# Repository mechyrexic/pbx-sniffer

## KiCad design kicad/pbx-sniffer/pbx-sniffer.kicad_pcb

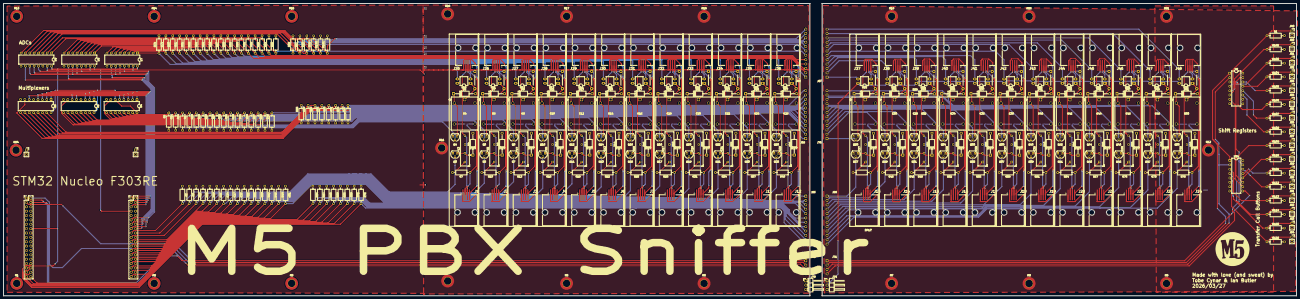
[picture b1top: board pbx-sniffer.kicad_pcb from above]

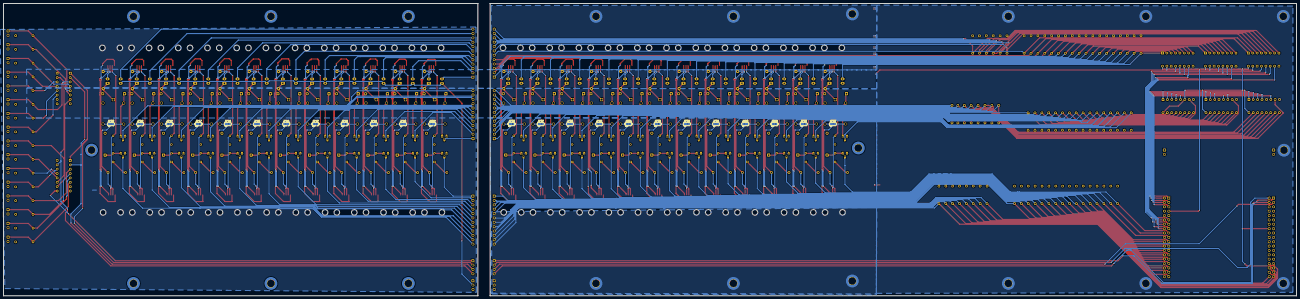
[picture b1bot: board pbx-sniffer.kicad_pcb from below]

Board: 2 copper layers, 752.5 x 170.1 mm, 432 parts (24 on the bottom side), 376 nets.

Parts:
D4, D5, D6, D7, D8, D9, D10, D11, D12, D13, D14, D15, D16, D17, D18, D19, D20, D21, D22, D23, D24, D25, D26, D27, D28, D29, D30, D31, D32, D33, D34, D35, D36, D37, D38, D39, D40, D41, D42, D43, D44, D45, D46, D47, D48, D49, D50, D51: D; D_A-405_P12.70mm_Horizontal
H1, H2, H3, H4, H5, H6, H7, H8, H9, H11, H12, H13, H14, H15, H16, H17, H18, H19, H20, H21, H24: MountingHole_Pad; MountingHole_4.3mm_M4_DIN965_Pad_TopBottom
J1, J2, J3, J4, J5, J6, J7, J8, J9, J10, J11, J12, J13, J14, J15, J16, J17, J18, J19, J20, J21, J22, J23, J24, J25, J26, J27, J28, J29, J30, J31, J32, J33, J34, J35, J36, J37, J38, J39, J40, J41, J42, J43, J44, J45, J46, J47, J48: Molex 0955016649
J49, J50, J51, J52, J53, J54, J55, J56, J57, J58, J59, J60, J61, J62, J63, J64: Conn_01x02_Socket; PinSocket_1x02_P2.54mm_Vertical
J65, J66, J67, J68, J69, J70: Conn_01x12_Pin; PinHeader_1x12_P2.54mm_Horizontal
J71, J72: Conn_01x04_Pin; PinHeader_1x04_P2.54mm_Horizontal
J73, J74: Conn_01x03_Pin; PinHeader_1x03_P2.54mm_Horizontal
JP2, JP3, JP4, JP5, JP6, JP7, JP8, JP9, JP10, JP11, JP12, JP13, JP14, JP15, JP16, JP17, JP18, JP19, JP20, JP21, JP22, JP23, JP24, JP25: JUP_P10mm
JP27, JP28, JP29, JP30, JP31, JP32, JP33, JP34, JP35, JP36, JP37, JP38, JP39, JP40, JP41, JP42, JP43, JP44, JP45, JP46, JP47, JP48, JP49, JP50: Jumper_3_Bridged12; SolderJumper-3_P1.3mm_Bridged2Bar12_RoundedPad1.0x1.5mm
K3, K5, K7, K9, K11, K13, K15, K17, K19, K21, K23, K25, K27, K29, K31, K33, K35, K37, K39, K41, K43, K45, K47, K49: Relay_SPST-NO; Relay_SPST_StandexMeder_SIL_Form1A
K4, K6, K8, K10, K12, K14, K16, K18, K20, K22, K24, K26, K28, K30, K32, K34, K36, K38, K40, K42, K44, K46, K48, K50: Relay_SPDT; K_AZ943-1C_AMZ
Q3, Q4, Q5, Q6, Q7, Q8, Q9, Q10, Q11, Q12, Q13, Q14, Q15, Q16, Q17, Q18, Q19, Q20, Q21, Q22, Q23, Q24, Q25, Q26, Q27, Q28, Q29, Q30, Q31, Q32, Q33, Q34, Q35, Q36, Q37, Q38, Q39, Q40, Q41, Q42, Q43, Q44, Q45, Q46, Q47, Q48, Q49, Q50: PMOS; TO-92_HandSolder
R1, R6, R8, R9, R11, R12, R14, R15, R17, R18, R20, R21, R23, R24, R26, R27, R29, R30, R32, R33, R35, R36, R38, R39, R41, R42, R44, R45, R47, R48, R50, R51, R53, R54, R56, R57, R59, R60, R62, R63, R65, R66, R68, R69, R71, R72, R74, R75, R77, R102, R103, R104, R105, R106, R107, R108, R109, R110, R111, R112, R113, R114, R115, R116: 10k; R_Axial_DIN0207_L6.3mm_D2.5mm_P10.16mm_Horizontal
R7, R10, R13, R16, R19, R22, R25, R28, R31, R34, R37, R40, R43, R46, R49, R52, R55, R58, R61, R64, R67, R70, R73, R76: 500; R_Axial_DIN0207_L6.3mm_D2.5mm_P10.16mm_Horizontal
R78, R79, R80, R81, R82, R83, R84, R85, R86, R87, R88, R89, R90, R91, R92, R93, R94, R95, R96, R97, R98, R99, R100, R101: R; R_Axial_DIN0207_L6.3mm_D2.5mm_P10.16mm_Horizontal
U1: STM32NucleoF303RE
U2, U34: 74LS165; DIP-16_W7.62mm
U4, U5, U6: 74HC138; DIP-16_W7.62mm
U7, U8, U9: MCP3008; DIP-16_W7.62mm
U10, U11, U12, U13, U14, U15, U16, U17, U18, U19, U20, U21, U22, U23, U24, U25, U26, U27, U28, U29, U30, U31, U32, U33: Optocoupler_DC_PhotoNPN_AKEC; DIP-4_W7.62mm_LongPads

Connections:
+3V3: U1.16 (+3V3), U1.33 (VBAT), U4.6 (E2), U4.16 (VCC), U5.16 (VCC), U6.16 (VCC), U7.16 (Vdd), U8.16 (Vdd), U9.16 (Vdd)
+5V: J49.2, J50.2, J51.2, J52.2, J53.2, J54.2, J55.2, J56.2, J57.2, J58.2, J59.2, J60.2, J61.2, J62.2, J63.2, J64.2, J73.1, J74.1, Q3.3 (S), Q4.3 (S), Q5.3 (S), Q6.3 (S), Q7.3 (S), Q8.3 (S), Q9.3 (S), Q10.3 (S), Q11.3 (S), Q12.3 (S), Q13.3 (S), Q14.3 (S), Q15.3 (S), Q16.3 (S), Q17.3 (S), Q18.3 (S), Q19.3 (S), Q20.3 (S), Q21.3 (S), Q22.3 (S), Q23.3 (S), Q24.3 (S), Q25.3 (S), Q26.3 (S), Q27.3 (S), Q28.3 (S), Q29.3 (S), Q30.3 (S), Q31.3 (S), Q32.3 (S), Q33.3 (S), Q34.3 (S), Q35.3 (S), Q36.3 (S), Q37.3 (S), Q38.3 (S), Q39.3 (S), Q40.3 (S), Q41.3 (S), Q42.3 (S), Q43.3 (S), Q44.3 (S), Q45.3 (S), Q46.3 (S), Q47.3 (S), Q48.3 (S), Q49.3 (S), Q50.3 (S), R6.1, R8.2, R9.1, R11.2, R12.1, R14.2, R15.1, R17.2, R18.1, R20.2, R21.1, R23.2, R24.1, R26.2, R27.1, R29.2, R30.1, R32.2, R33.1, R35.2, R36.1, R38.2, R39.1, R41.2, R42.1, R44.2, R45.1, R47.2, R48.1, R50.2, R51.1, R53.2, R54.1, R56.2, R57.1, R59.2, R60.1, R62.2, R63.1, R65.2, R66.1, R68.2, R69.1, R71.2, R72.1, R74.2, R75.1, R77.2, U1.18 (+5V), U2.16 (VCC), U34.16 (VCC)
/ADC/ADC0: R78.1, U7.1 (CH0), U10.3
/ADC/ADC1: R79.1, U7.2 (CH1), U11.3
/ADC/ADC2: R80.1, U7.3 (CH2), U12.3
/ADC/ADC3: R81.1, U7.4 (CH3), U13.3
/ADC/ADC4: R82.1, U7.5 (CH4), U14.3
/ADC/ADC5: R83.1, U7.6 (CH5), U15.3
/ADC/ADC6: R84.1, U7.7 (CH6), U16.3
/ADC/ADC7: R85.1, U7.8 (CH7), U17.3
/ADC/ADC8: R86.1, U8.1 (CH0), U18.3
/ADC/ADC9: R87.1, U8.2 (CH1), U19.3
/ADC/ADC10: R88.1, U8.3 (CH2), U20.3
/ADC/ADC11: R89.1, U8.4 (CH3), U21.3
/ADC/ADC12: J67.1, J68.1, R90.1, U8.5 (CH4), U22.3
/ADC/ADC13: J67.2, J68.2, R91.1, U8.6 (CH5), U23.3
/ADC/ADC14: J67.3, J68.3, R92.1, U8.7 (CH6), U24.3
/ADC/ADC15: J67.4, J68.4, R93.1, U8.8 (CH7), U25.3
/ADC/ADC16: J67.5, J68.5, R94.1, U9.1 (CH0), U26.3
/ADC/ADC17: J67.6, J68.6, R95.1, U9.2 (CH1), U27.3
/ADC/ADC18: J67.7, J68.7, R96.1, U9.3 (CH2), U28.3
/ADC/ADC19: J67.8, J68.8, R97.1, U9.4 (CH3), U29.3
/ADC/ADC20: J67.9, J68.9, R98.1, U9.5 (CH4), U30.3
/ADC/ADC21: J67.10, J68.10, R99.1, U9.6 (CH5), U31.3
/ADC/ADC22: J67.11, J68.11, R100.1, U9.7 (CH6), U32.3
/ADC/ADC23: J67.12, J68.12, R101.1, U9.8 (CH7), U33.3
/Input Phone Jacks/Line Control0/Tpbx: J1.2, JP27.2 (C), R7.1
/Input Phone Jacks/Line Control1/Tpbx: J2.2, JP28.2 (C), R10.1
/Input Phone Jacks/Line Control2/Tpbx: J3.2, JP29.2 (C), R13.1
/Input Phone Jacks/Line Control3/Tpbx: J4.2, JP30.2 (C), R16.1
/Input Phone Jacks/Line Control4/Tpbx: J5.2, JP31.2 (C), R19.1
/Input Phone Jacks/Line Control5/Tpbx: J6.2, JP32.2 (C), R22.1
/Input Phone Jacks/Line Control6/Tpbx: J7.2, JP33.2 (C), R25.1
/Input Phone Jacks/Line Control7/Tpbx: J8.2, JP34.2 (C), R28.1
/Input Phone Jacks/Line Control8/Tpbx: J9.2, JP35.2 (C), R31.1
/Input Phone Jacks/Line Control9/Tpbx: J10.2, JP36.2 (C), R34.1
/Input Phone Jacks/Line Control10/Tpbx: J11.2, JP37.2 (C), R37.1
/Input Phone Jacks/Line Control11/Tpbx: J12.2, JP38.2 (C), R40.1
/Input Phone Jacks/Line Control12/Tpbx: J13.2, JP39.2 (C), R43.1
/Input Phone Jacks/Line Control13/Tpbx: J14.2, JP40.2 (C), R46.1
/Input Phone Jacks/Line Control14/Tpbx: J15.2, JP41.2 (C), R49.1
/Input Phone Jacks/Line Control15/Tpbx: J16.2, JP42.2 (C), R52.1
/Input Phone Jacks/Line Control16/Tpbx: J17.2, JP43.2 (C), R55.1
/Input Phone Jacks/Line Control17/Tpbx: J18.2, JP44.2 (C), R58.1
/Input Phone Jacks/Line Control18/Tpbx: J19.2, JP45.2 (C), R61.1
/Input Phone Jacks/Line Control19/Tpbx: J20.2, JP46.2 (C), R64.1
/Input Phone Jacks/Line Control20/Tpbx: J21.2, JP47.2 (C), R67.1
/Input Phone Jacks/Line Control21/Tpbx: J22.2, JP48.2 (C), R70.1
/Input Phone Jacks/Line Control22/Tpbx: J23.2, JP49.2 (C), R73.1
/Input Phone Jacks/Line Control23/Tpbx: J24.2, JP50.2 (C), R76.1
/Input Phone Jacks/Rpbx0: J1.3, J25.3, K3.7
/Input Phone Jacks/Rpbx1: J2.3, J26.3, K5.7
/Input Phone Jacks/Rpbx2: J3.3, J27.3, K7.7
/Input Phone Jacks/Rpbx3: J4.3, J28.3, K9.7
/Input Phone Jacks/Rpbx4: J5.3, J29.3, K11.7
/Input Phone Jacks/Rpbx5: J6.3, J30.3, K13.7
/Input Phone Jacks/Rpbx6: J7.3, J31.3, K15.7
/Input Phone Jacks/Rpbx7: J8.3, J32.3, K17.7
/Input Phone Jacks/Rpbx8: J9.3, J33.3, K19.7
/Input Phone Jacks/Rpbx9: J10.3, J34.3, K21.7
/Input Phone Jacks/Rpbx10: J11.3, J35.3, K23.7
/Input Phone Jacks/Rpbx11: J12.3, J36.3, K25.7
/Input Phone Jacks/Rpbx12: J13.3, J37.3, K27.7
/Input Phone Jacks/Rpbx13: J14.3, J38.3, K29.7
/Input Phone Jacks/Rpbx14: J15.3, J39.3, K31.7
/Input Phone Jacks/Rpbx15: J16.3, J40.3, K33.7
/Input Phone Jacks/Rpbx16: J17.3, J41.3, K35.7
/Input Phone Jacks/Rpbx17: J18.3, J42.3, K37.7
/Input Phone Jacks/Rpbx18: J19.3, J43.3, K39.7
/Input Phone Jacks/Rpbx19: J20.3, J44.3, K41.7
/Input Phone Jacks/Rpbx20: J21.3, J45.3, K43.7
/Input Phone Jacks/Rpbx21: J22.3, J46.3, K45.7
/Input Phone Jacks/Rpbx22: J23.3, J47.3, K47.7
/Input Phone Jacks/Rpbx23: J24.3, J48.3, K49.7
/Input Phone Jacks/Tpbx0: JP2.2, K4.1, U10.1
/Input Phone Jacks/Tpbx1: JP3.2, K6.1, U11.1
/Input Phone Jacks/Tpbx2: JP4.2, K8.1, U12.1
/Input Phone Jacks/Tpbx3: JP5.2, K10.1, U13.1
/Input Phone Jacks/Tpbx4: JP6.2, K12.1, U14.1
/Input Phone Jacks/Tpbx5: JP7.2, K14.1, U15.1
/Input Phone Jacks/Tpbx6: JP8.2, K16.1, U16.1
/Input Phone Jacks/Tpbx7: JP9.2, K18.1, U17.1
/Input Phone Jacks/Tpbx8: JP10.2, K20.1, U18.1
/Input Phone Jacks/Tpbx9: JP11.2, K22.1, U19.1
/Input Phone Jacks/Tpbx10: JP12.2, K24.1, U20.1
/Input Phone Jacks/Tpbx11: JP13.2, K26.1, U21.1
/Input Phone Jacks/Tpbx12: JP14.2, K28.1, U22.1
/Input Phone Jacks/Tpbx13: JP15.2, K30.1, U23.1
/Input Phone Jacks/Tpbx14: JP16.2, K32.1, U24.1
/Input Phone Jacks/Tpbx15: JP17.2, K34.1, U25.1
/Input Phone Jacks/Tpbx16: JP18.2, K36.1, U26.1
/Input Phone Jacks/Tpbx17: JP19.2, K38.1, U27.1
/Input Phone Jacks/Tpbx18: JP20.2, K40.1, U28.1
/Input Phone Jacks/Tpbx19: JP21.2, K42.1, U29.1
/Input Phone Jacks/Tpbx20: JP22.2, K44.1, U30.1
/Input Phone Jacks/Tpbx21: JP23.2, K46.1, U31.1
/Input Phone Jacks/Tpbx22: JP24.2, K48.1, U32.1
/Input Phone Jacks/Tpbx23: JP25.2, K50.1, U33.1
/Input Phone Jacks/ptRX0: J1.4, J25.4
/Input Phone Jacks/ptRX1: J2.4, J26.4
/Input Phone Jacks/ptRX2: J3.4, J27.4
/Input Phone Jacks/ptRX3: J4.4, J28.4
/Input Phone Jacks/ptRX4: J5.4, J29.4
/Input Phone Jacks/ptRX5: J6.4, J30.4
/Input Phone Jacks/ptRX6: J7.4, J31.4
/Input Phone Jacks/ptRX7: J8.4, J32.4
/Input Phone Jacks/ptRX8: J9.4, J33.4
/Input Phone Jacks/ptRX9: J10.4, J34.4
/Input Phone Jacks/ptRX10: J11.4, J35.4
/Input Phone Jacks/ptRX11: J12.4, J36.4
/Input Phone Jacks/ptRX12: J13.4, J37.4
/Input Phone Jacks/ptRX13: J14.4, J38.4
/Input Phone Jacks/ptRX14: J15.4, J39.4
/Input Phone Jacks/ptRX15: J16.4, J40.4
/Input Phone Jacks/ptRX16: J17.4, J41.4
/Input Phone Jacks/ptRX17: J18.4, J42.4
/Input Phone Jacks/ptRX18: J19.4, J43.4
/Input Phone Jacks/ptRX19: J20.4, J44.4
/Input Phone Jacks/ptRX20: J21.4, J45.4
/Input Phone Jacks/ptRX21: J22.4, J46.4
/Input Phone Jacks/ptRX22: J23.4, J47.4
/Input Phone Jacks/ptRX23: J24.4, J48.4
/Input Phone Jacks/ptTX0: J1.1, J25.1
/Input Phone Jacks/ptTX1: J2.1, J26.1
/Input Phone Jacks/ptTX2: J3.1, J27.1
/Input Phone Jacks/ptTX3: J4.1, J28.1
/Input Phone Jacks/ptTX4: J5.1, J29.1
/Input Phone Jacks/ptTX5: J6.1, J30.1
/Input Phone Jacks/ptTX6: J7.1, J31.1
/Input Phone Jacks/ptTX7: J8.1, J32.1
/Input Phone Jacks/ptTX8: J9.1, J33.1
/Input Phone Jacks/ptTX9: J10.1, J34.1
/Input Phone Jacks/ptTX10: J11.1, J35.1
/Input Phone Jacks/ptTX11: J12.1, J36.1
/Input Phone Jacks/ptTX12: J13.1, J37.1
/Input Phone Jacks/ptTX13: J14.1, J38.1
/Input Phone Jacks/ptTX14: J15.1, J39.1
/Input Phone Jacks/ptTX15: J16.1, J40.1
/Input Phone Jacks/ptTX16: J17.1, J41.1
/Input Phone Jacks/ptTX17: J18.1, J42.1
/Input Phone Jacks/ptTX18: J19.1, J43.1
/Input Phone Jacks/ptTX19: J20.1, J44.1
/Input Phone Jacks/ptTX20: J21.1, J45.1
/Input Phone Jacks/ptTX21: J22.1, J46.1
/Input Phone Jacks/ptTX22: J23.1, J47.1
/Input Phone Jacks/ptTX23: J24.1, J48.1
/Multiplexers/LineControl0: Q4.2 (G), R8.1, U4.15 (~Y0)
/Multiplexers/LineControl1: Q6.2 (G), R11.1, U4.14 (~Y1)
/Multiplexers/LineControl2: Q8.2 (G), R14.1, U4.13 (~Y2)
/Multiplexers/LineControl3: Q10.2 (G), R17.1, U4.12 (~Y3)
/Multiplexers/LineControl4: Q12.2 (G), R20.1, U4.11 (~Y4)
/Multiplexers/LineControl5: Q14.2 (G), R23.1, U4.10 (~Y5)
/Multiplexers/LineControl6: Q16.2 (G), R26.1, U4.9 (~Y6)
/Multiplexers/LineControl7: Q18.2 (G), R29.1, U4.7 (~Y7)
/Multiplexers/LineControl8: Q20.2 (G), R32.1, U5.15 (~Y0)
/Multiplexers/LineControl9: Q22.2 (G), R35.1, U5.14 (~Y1)
/Multiplexers/LineControl10: Q24.2 (G), R38.1, U5.13 (~Y2)
/Multiplexers/LineControl11: Q26.2 (G), R41.1, U5.12 (~Y3)
/Multiplexers/LineControl12: J69.1, J70.1, Q28.2 (G), R44.1, U5.11 (~Y4)
/Multiplexers/LineControl13: J69.2, J70.2, Q30.2 (G), R47.1, U5.10 (~Y5)
/Multiplexers/LineControl14: J69.3, J70.3, Q32.2 (G), R50.1, U5.9 (~Y6)
/Multiplexers/LineControl15: J69.4, J70.4, Q34.2 (G), R53.1, U5.7 (~Y7)
/Multiplexers/LineControl16: J69.5, J70.5, Q36.2 (G), R56.1, U6.15 (~Y0)
/Multiplexers/LineControl17: J69.6, J70.6, Q38.2 (G), R59.1, U6.14 (~Y1)
/Multiplexers/LineControl18: J69.7, J70.7, Q40.2 (G), R62.1, U6.13 (~Y2)
/Multiplexers/LineControl19: J69.8, J70.8, Q42.2 (G), R65.1, U6.12 (~Y3)
/Multiplexers/LineControl20: J69.9, J70.9, Q44.2 (G), R68.1, U6.11 (~Y4)
/Multiplexers/LineControl21: J69.10, J70.10, Q46.2 (G), R71.1, U6.10 (~Y5)
/Multiplexers/LineControl22: J69.11, J70.11, Q48.2 (G), R74.1, U6.9 (~Y6)
/Multiplexers/LineControl23: J69.12, J70.12, Q50.2 (G), R77.1, U6.7 (~Y7)
/Output Phone Jacks/Wiretap0/Tpots: J25.2, JP2.1, U10.2
/Output Phone Jacks/Wiretap1/Tpots: J26.2, JP3.1, U11.2
/Output Phone Jacks/Wiretap2/Tpots: J27.2, JP4.1, U12.2
/Output Phone Jacks/Wiretap3/Tpots: J28.2, JP5.1, U13.2
/Output Phone Jacks/Wiretap4/Tpots: J29.2, JP6.1, U14.2
/Output Phone Jacks/Wiretap5/Tpots: J30.2, JP7.1, U15.2
/Output Phone Jacks/Wiretap6/Tpots: J31.2, JP8.1, U16.2
/Output Phone Jacks/Wiretap7/Tpots: J32.2, JP9.1, U17.2
/Output Phone Jacks/Wiretap8/Tpots: J33.2, JP10.1, U18.2
/Output Phone Jacks/Wiretap9/Tpots: J34.2, JP11.1, U19.2
/Output Phone Jacks/Wiretap10/Tpots: J35.2, JP12.1, U20.2
/Output Phone Jacks/Wiretap11/Tpots: J36.2, JP13.1, U21.2
/Output Phone Jacks/Wiretap12/Tpots: J37.2, JP14.1, U22.2
/Output Phone Jacks/Wiretap13/Tpots: J38.2, JP15.1, U23.2
/Output Phone Jacks/Wiretap14/Tpots: J39.2, JP16.1, U24.2
/Output Phone Jacks/Wiretap15/Tpots: J40.2, JP17.1, U25.2
/Output Phone Jacks/Wiretap16/Tpots: J41.2, JP18.1, U26.2
/Output Phone Jacks/Wiretap17/Tpots: J42.2, JP19.1, U27.2
/Output Phone Jacks/Wiretap18/Tpots: J43.2, JP20.1, U28.2
/Output Phone Jacks/Wiretap19/Tpots: J44.2, JP21.1, U29.2
/Output Phone Jacks/Wiretap20/Tpots: J45.2, JP22.1, U30.2
/Output Phone Jacks/Wiretap21/Tpots: J46.2, JP23.1, U31.2
/Output Phone Jacks/Wiretap22/Tpots: J47.2, JP24.1, U32.2
/Output Phone Jacks/Wiretap23/Tpots: J48.2, JP25.1, U33.2
/Shift Registers/TBTN0: J49.1, R1.1, U2.6 (D7)
/Shift Registers/TBTN1: J50.1, R102.1, U2.5 (D6)
/Shift Registers/TBTN2: J51.1, R103.1, U2.4 (D5)
/Shift Registers/TBTN3: J54.1, R106.1, U2.3 (D4)
/Shift Registers/TBTN4: J53.1, R105.1, U2.14 (D3)
/Shift Registers/TBTN5: J52.1, R104.1, U2.13 (D2)
/Shift Registers/TBTN6: J55.1, R107.1, U2.12 (D1)
/Shift Registers/TBTN7: J56.1, R108.1, U2.11 (D0)
/Shift Registers/TBTN8: J64.1, R116.1, U34.6 (D7)
/Shift Registers/TBTN9: J63.1, R115.1, U34.5 (D6)
/Shift Registers/TBTN10: J62.1, R114.1, U34.4 (D5)
/Shift Registers/TBTN11: J61.1, R113.1, U34.3 (D4)
/Shift Registers/TBTN12: J60.1, R112.1, U34.14 (D3)
/Shift Registers/TBTN13: J59.1, R111.1, U34.13 (D2)
/Shift Registers/TBTN14: J58.1, R110.1, U34.12 (D1)
/Shift Registers/TBTN15: J57.1, R109.1, U34.11 (D0)
Cline0: U1.41 (PC9), U4.1 (A0), U5.1 (A0), U6.1 (A0)
Cline1: U1.42 (PC8), U4.2 (A1), U5.2 (A1), U6.2 (A1)
Cline2: U1.43 (PB8), U4.3 (A2), U5.3 (A2), U6.3 (A2)
Cline3: U1.44 (PC6), U4.4 (~E0), U5.6 (E2), U6.4 (~E0)
Cline4: U1.45 (PB9), U4.5 (~E1), U5.5 (~E1), U6.6 (E2)
GNDD: D4.2 (A), D5.2 (A), D6.2 (A), D7.2 (A), D8.2 (A), D9.2 (A), D10.2 (A), D11.2 (A), D12.2 (A), D13.2 (A), D14.2 (A), D15.2 (A), D16.2 (A), D17.2 (A), D18.2 (A), D19.2 (A), D20.2 (A), D21.2 (A), D22.2 (A), D23.2 (A), D24.2 (A), D25.2 (A), D26.2 (A), D27.2 (A), D28.2 (A), D29.2 (A), D30.2 (A), D31.2 (A), D32.2 (A), D33.2 (A), D34.2 (A), D35.2 (A), D36.2 (A), D37.2 (A), D38.2 (A), D39.2 (A), D40.2 (A), D41.2 (A), D42.2 (A), D43.2 (A), D44.2 (A), D45.2 (A), D46.2 (A), D47.2 (A), D48.2 (A), D49.2 (A), D50.2 (A), D51.2 (A), H1.1, H2.1, H3.1, H4.1, H5.1, H6.1, H7.1, H8.1, H9.1, H11.1, H12.1, H13.1, H14.1, H15.1, H16.1, H17.1, H18.1, H19.1, H20.1, H21.1, H24.1, J73.3, J74.3, K3.5, K4.5, K5.5, K6.5, K7.5, K8.5, K9.5, K10.5, K11.5, K12.5, K13.5, K14.5, K15.5, K16.5, K17.5, K18.5, K19.5, K20.5, K21.5, K22.5, K23.5, K24.5, K25.5, K26.5, K27.5, K28.5, K29.5, K30.5, K31.5, K32.5, K33.5, K34.5, K35.5, K36.5, K37.5, K38.5, K39.5, K40.5, K41.5, K42.5, K43.5, K44.5, K45.5, K46.5, K47.5, K48.5, K49.5, K50.5, R1.2, R78.2, R79.2, R80.2, R81.2, R82.2, R83.2, R84.2, R85.2, R86.2, R87.2, R88.2, R89.2, R90.2, R91.2, R92.2, R93.2, R94.2, R95.2, R96.2, R97.2, R98.2, R99.2, R100.2, R101.2, R102.2, R103.2, R104.2, R105.2, R106.2, R107.2, R108.2, R109.2, R110.2, R111.2, R112.2, R113.2, R114.2, R115.2, R116.2, U1.8 (GND), U1.19 (GND), U1.20 (GND), U1.22 (GND), U1.39 (GND), U1.40 (GND), U1.49 (GND), U1.60 (GND), U1.72 (AGND), U2.8 (GND), U4.8 (GND), U5.4 (~E0), U5.8 (GND), U6.5 (~E1), U6.8 (GND), U7.9 (DGND), U7.14 (AGND), U8.9 (DGND), U8.14 (AGND), U9.9 (DGND), U9.14 (AGND), U34.8 (GND)
unnamed: D4.1 (K), K3.3, Q3.1 (D)
unnamed: D5.1 (K), K4.2, Q4.1 (D)
unnamed: D6.1 (K), K5.3, Q5.1 (D)
unnamed: D7.1 (K), K6.2, Q6.1 (D)
unnamed: D8.1 (K), K7.3, Q7.1 (D)
unnamed: D9.1 (K), K8.2, Q8.1 (D)
unnamed: D10.1 (K), K9.3, Q9.1 (D)
unnamed: D11.1 (K), K10.2, Q10.1 (D)
unnamed: D12.1 (K), K11.3, Q11.1 (D)
unnamed: D13.1 (K), K12.2, Q12.1 (D)
unnamed: D14.1 (K), K13.3, Q13.1 (D)
unnamed: D15.1 (K), K14.2, Q14.1 (D)
unnamed: D16.1 (K), K15.3, Q15.1 (D)
unnamed: D17.1 (K), K16.2, Q16.1 (D)
unnamed: D18.1 (K), K17.3, Q17.1 (D)
unnamed: D19.1 (K), K18.2, Q18.1 (D)
unnamed: D20.1 (K), K19.3, Q19.1 (D)
unnamed: D21.1 (K), K20.2, Q20.1 (D)
unnamed: D22.1 (K), K21.3, Q21.1 (D)
unnamed: D23.1 (K), K22.2, Q22.1 (D)
unnamed: D24.1 (K), K23.3, Q23.1 (D)
unnamed: D25.1 (K), K24.2, Q24.1 (D)
unnamed: D26.1 (K), K25.3, Q25.1 (D)
unnamed: D27.1 (K), K26.2, Q26.1 (D)
unnamed: D28.1 (K), K27.3, Q27.1 (D)
unnamed: D29.1 (K), K28.2, Q28.1 (D)
unnamed: D30.1 (K), K29.3, Q29.1 (D)
unnamed: D31.1 (K), K30.2, Q30.1 (D)
unnamed: D32.1 (K), K31.3, Q31.1 (D)
unnamed: D33.1 (K), K32.2, Q32.1 (D)
unnamed: D34.1 (K), K33.3, Q33.1 (D)
unnamed: D35.1 (K), K34.2, Q34.1 (D)
unnamed: D36.1 (K), K35.3, Q35.1 (D)
unnamed: D37.1 (K), K36.2, Q36.1 (D)
unnamed: D38.1 (K), K37.3, Q37.1 (D)
unnamed: D39.1 (K), K38.2, Q38.1 (D)
unnamed: D40.1 (K), K39.3, Q39.1 (D)
unnamed: D41.1 (K), K40.2, Q40.1 (D)
unnamed: D42.1 (K), K41.3, Q41.1 (D)
unnamed: D43.1 (K), K42.2, Q42.1 (D)
unnamed: D44.1 (K), K43.3, Q43.1 (D)
unnamed: D45.1 (K), K44.2, Q44.1 (D)
unnamed: D46.1 (K), K45.3, Q45.1 (D)
unnamed: D47.1 (K), K46.2, Q46.1 (D)
unnamed: D48.1 (K), K47.3, Q47.1 (D)
unnamed: D49.1 (K), K48.2, Q48.1 (D)
unnamed: D50.1 (K), K49.3, Q49.1 (D)
unnamed: D51.1 (K), K50.2, Q50.1 (D)
unnamed: J72.1, U1.1 (PC10)
unnamed: J72.2, U1.2 (PC11)
unnamed: J72.3, U1.3 (PC12)
unnamed: J72.4, U1.4 (PD12)
unnamed: JP27.1 (A), K4.4
unnamed: JP27.3 (B), K4.3
unnamed: JP28.1 (A), K6.4
unnamed: JP28.3 (B), K6.3
unnamed: JP29.1 (A), K8.4
unnamed: JP29.3 (B), K8.3
unnamed: JP30.1 (A), K10.4
unnamed: JP30.3 (B), K10.3
unnamed: JP31.1 (A), K12.4
unnamed: JP31.3 (B), K12.3
unnamed: JP32.1 (A), K14.4
unnamed: JP32.3 (B), K14.3
unnamed: JP33.1 (A), K16.4
unnamed: JP33.3 (B), K16.3
unnamed: JP34.1 (A), K18.4
unnamed: JP34.3 (B), K18.3
unnamed: JP35.1 (A), K20.4
unnamed: JP35.3 (B), K20.3
unnamed: JP36.1 (A), K22.4
unnamed: JP36.3 (B), K22.3
unnamed: JP37.1 (A), K24.4
unnamed: JP37.3 (B), K24.3
unnamed: JP38.1 (A), K26.4
unnamed: JP38.3 (B), K26.3
unnamed: JP39.1 (A), K28.4
unnamed: JP39.3 (B), K28.3
unnamed: JP40.1 (A), K30.4
unnamed: JP40.3 (B), K30.3
unnamed: JP41.1 (A), K32.4
unnamed: JP41.3 (B), K32.3
unnamed: JP42.1 (A), K34.4
unnamed: JP42.3 (B), K34.3
unnamed: JP43.1 (A), K36.4
unnamed: JP43.3 (B), K36.3
unnamed: JP44.1 (A), K38.4
unnamed: JP44.3 (B), K38.3
unnamed: JP45.1 (A), K40.4
unnamed: JP45.3 (B), K40.3
unnamed: JP46.1 (A), K42.4
unnamed: JP46.3 (B), K42.3
unnamed: JP47.1 (A), K44.4
unnamed: JP47.3 (B), K44.3
unnamed: JP48.1 (A), K46.4
unnamed: JP48.3 (B), K46.3
unnamed: JP49.1 (A), K48.4
unnamed: JP49.3 (B), K48.3
unnamed: JP50.1 (A), K50.4
unnamed: JP50.3 (B), K50.3
unnamed: K3.1, R7.2
unnamed: K5.1, R10.2
unnamed: K7.1, R13.2
unnamed: K9.1, R16.2
unnamed: K11.1, R19.2
unnamed: K13.1, R22.2
unnamed: K15.1, R25.2
unnamed: K17.1, R28.2
unnamed: K19.1, R31.2
unnamed: K21.1, R34.2
unnamed: K23.1, R37.2
unnamed: K25.1, R40.2
unnamed: K27.1, R43.2
unnamed: K29.1, R46.2
unnamed: K31.1, R49.2
unnamed: K33.1, R52.2
unnamed: K35.1, R55.2
unnamed: K37.1, R58.2
unnamed: K39.1, R61.2
unnamed: K41.1, R64.2
unnamed: K43.1, R67.2
unnamed: K45.1, R70.2
unnamed: K47.1, R73.2
unnamed: K49.1, R76.2
unnamed: U2.7 (~Q7), U34.10 (DS)
VDDA: J73.2, J74.2, U1.47 (AVDD), U7.15 (Vref), U8.15 (Vref), U9.15 (Vref), U10.4, U11.4, U12.4, U13.4, U14.4, U15.4, U16.4, U17.4, U18.4, U19.4, U20.4, U21.4, U22.4, U23.4, U24.4, U25.4, U26.4, U27.4, U28.4, U29.4, U30.4, U31.4, U32.4, U33.4
hookSW0: Q3.2 (G), R6.2, U1.57 (PB6)
hookSW1: Q5.2 (G), R9.2, U1.58 (PB11)
hookSW2: Q7.2 (G), R12.2, U1.59 (PC7)
hookSW3: Q9.2 (G), R15.2, U1.61 (PA9)
hookSW4: Q11.2 (G), R18.2, U1.62 (PB2)
hookSW5: Q13.2 (G), R21.2, U1.63 (PA8)
hookSW6: Q15.2 (G), R24.2, U1.64 (PB1)
hookSW7: Q17.2 (G), R27.2, U1.65 (PB10)
hookSW8: Q19.2 (G), R30.2, U1.66 (PB15)
hookSW9: Q21.2 (G), R33.2, U1.67 (PB4)
hookSW10: Q23.2 (G), R36.2, U1.68 (PB14)
hookSW11: Q25.2 (G), R39.2, U1.69 (PB5)
hookSW12: J65.1, J66.1, Q27.2 (G), R42.2, U1.70 (PB13)
hookSW13: J65.2, J66.2, Q29.2 (G), R45.2, U1.71 (PB3)
hookSW14: J65.3, J66.3, Q31.2 (G), R48.2, U1.73 (PA10)
hookSW15: J65.4, J66.4, Q33.2 (G), R51.2, U1.74 (PC4)
hookSW16: J65.5, J66.5, Q35.2 (G), R54.2, U1.75 (PA2)
hookSW17: J65.6, J66.6, Q37.2 (G), R57.2, U1.77 (PA3)
hookSW18: J65.7, J66.7, Q39.2 (G), R60.2, U1.38 (PC0)
hookSW19: J65.8, J66.8, Q41.2 (G), R63.2, U1.37 (PC3)
hookSW20: J65.9, J66.9, Q43.2 (G), R66.2, U1.36 (PC1)
hookSW21: J65.10, J66.10, Q45.2 (G), R69.2, U1.35 (PC2)
hookSW22: J65.11, J66.11, Q47.2 (G), R72.2, U1.34 (PB0)
hookSW23: J65.12, J66.12, Q49.2 (G), R75.2, U1.32 (PA4)
shiftClk: J71.3, U2.2 (CP), U34.2 (CP)
shiftInh: J71.4, U2.15 (~CE), U34.15 (~CE)
shiftLd: J71.2, U2.1 (~PL), U34.1 (~PL)
shiftOut: J71.1, U34.9 (Q7)
spi0clk: U1.51 (PA5), U7.13 (CLK), U8.13 (CLK), U9.13 (CLK)
spi0cs0: U1.52 (PA12), U7.10 (~CS/SHDN)
spi0cs1: U1.54 (PA11), U8.10 (~CS/SHDN)
spi0cs2: U1.56 (PB12), U9.10 (~CS/SHDN)
spi0miso: U1.53 (PA6), U7.12 (Dout), U8.12 (Dout), U9.12 (Dout)
spi0mosi: U1.55 (PA7), U7.11 (Din), U8.11 (Din), U9.11 (Din)

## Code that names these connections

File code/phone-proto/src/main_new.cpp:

#include <Arduino.h>
#include <SPI.h>
// TODO use relative timestamps

//#define LINE_CTRL_PIN D2
//#define OFFHOOK_CTRL_PIN D3
#define NUM_PHONES 24
#define NUM_TRANSFER_BTNS 16
#define NUM_ADCS 3
#define SAMPLE_BUFFER_SIZE 32
#define PHONE_DIGITS 10
#define SPI_F 2340

const uint8_t dial_test_pin = PA1;

#define MAX_DIAL_LEN 4 // Enough for "101", "111", etc.
#define BAIRD_INDEX 11

// Extension Numbers (PBX Logic: '0' is 10 pulses)
const uint8_t NUMBER_BAIRD[] = {1, 10, 1}; // "101"
const uint8_t NUMBER_JK[]   = {1, 10, 9};  // "109"

// Panasonic KX-TA824 Timings
#define T_PULSE_BREAK 60   // On-hook (Relay OFF / Pin HIGH)
#define T_PULSE_MAKE 40    // Off-hook (Relay ON / Pin LOW)
#define T_DIGIT_GAP 800    
#define T_HOOK_Hookswitch 600   
#define T_STABILIZE 500    

const uint8_t line_ctrls[] = { PC9, PC8, PB8, PC6, PB9 };
const uint8_t offhook_ctrls[] = {
  PB6, PB11, PC7, PA9, PB2, PA8, PB1, PB10, PB15, PB4, PB14, PB5,
  PB13, PB3, PA10, PC4, PA2, PA3, PC0, PC3, PC1, PC2, PB0, PA4
};

// Shift Register Pins
const uint8_t transfer_shiftld_pin = PC11;
const uint8_t transfer_shiftout_pin = PC10;
const uint8_t transfer_shiftclk_pin = PC12;
const uint8_t transfer_shiftinh_pin = PD2;

enum SeqState {
  IDLE,
  LOCAL_PICKUP,     // 1. Offhook Local
  LOCAL_DIAL_HOST,  // 2. Dial Baird
  WAIT_FOR_HOST,    // 3. Wait 5s
  LOCAL_HOOKSWITCH,      // 4. Hookswitch Local
  LOCAL_HANGUP,     // 5 & 6. Hangup & Release Local
  HOST_PICKUP,      // 7 & 8. Control Host & Offhook
  HOST_DIAL_JK,     // 9. Dial JK
  WAIT_FOR_JK,      // 10. Wait 3s
  HOST_Hookswitch,       // 11. Final Hookswitch
  CLEANUP           // 12. Release everything
};

struct PhoneTask {
  SeqState state = IDLE;
  uint32_t next_ms = 0;
  uint8_t dial_buf[MAX_DIAL_LEN];
  uint8_t dial_pos = 0;
  uint8_t pulses_left = 0;
  bool is_break = false;
  uint8_t active_index = 0;
};

PhoneTask task;
uint32_t curtime = 0;

void line_ctrl_mux_select(uint8_t index) {
  for (int i = 0; i < sizeof(line_ctrls)/sizeof(line_ctrls[0]); i++) {
    digitalWrite(line_ctrls[i], (index >> i) & 0x01);
  }
}

void set_hook(uint8_t index, bool offhook) {
  // Active-Low: LOW = Energized = Off-hook
  digitalWrite(offhook_ctrls[index], offhook ? LOW : HIGH);
}

bool process_dialing(uint8_t index) {
  if (task.pulses_left == 0) {
    task.dial_pos++;
    if (task.dial_pos >= 3) return true; // Done
    task.pulses_left = task.dial_buf[task.dial_pos];
    task.next_ms = curtime + T_DIGIT_GAP;
    return false;
  }

  if (task.is_break) {
    set_hook(index, true); // Close (Off-hook)
    task.is_break = false;
    task.pulses_left--;
    task.next_ms = curtime + T_PULSE_MAKE;
  } else {
    set_hook(index, false); // Open (On-hook)
    task.is_break = true;
    task.next_ms = curtime + T_PULSE_BREAK;
  }
  return false;
}

void run_sequence() {
  if (task.state == IDLE || curtime < task.next_ms) return;

  switch (task.state) {
    case LOCAL_PICKUP:
      line_ctrl_mux_select(task.active_index);
      set_hook(task.active_index, true);
      memcpy(task.dial_buf, NUMBER_BAIRD, 3);
      task.dial_pos = 0;
      task.pulses_left = task.dial_buf[0];
      task.state = LOCAL_DIAL_HOST;
      task.next_ms = curtime + T_STABILIZE;
      break;

    case LOCAL_DIAL_HOST:
      if (process_dialing(task.active_index)) {
        task.state = WAIT_FOR_HOST;
        task.next_ms = curtime + 5000;
      }
      break;

    case WAIT_FOR_HOST:
      set_hook(task.active_index, false); // Start Hookswitch
      task.state = LOCAL_HOOKSWITCH;
      task.next_ms = curtime + T_HOOK_Hookswitch;
      break;

    case LOCAL_HOOKSWITCH:
      set_hook(task.active_index, true); // End Hookswitch
      task.state = LOCAL_HANGUP;
      task.next_ms = curtime + T_STABILIZE;
      break;

    case LOCAL_HANGUP:
      set_hook(task.active_index, false); // Hangup
      line_ctrl_mux_select(0); // Release Mux
      task.state = HOST_PICKUP;
      task.next_ms = curtime + 500;
      break;

    case HOST_PICKUP:
      task.active_index = BAIRD_INDEX;
      line_ctrl_mux_select(task.active_index);
      set_hook(task.active_index, true);
      memcpy(task.dial_buf, NUMBER_JK, 3);
      task.dial_pos = 0;
      task.pulses_left = task.dial_buf[0];
      task.state = HOST_DIAL_JK;
      task.next_ms = curtime + T_STABILIZE;
      break;

    case HOST_DIAL_JK:
      if (process_dialing(task.active_index)) {
        task.state = WAIT_FOR_JK;
        task.next_ms = curtime + 3000;
      }
      break;

    case WAIT_FOR_JK:
      set_hook(task.active_index, false); // Start Hookswitch
      task.state = HOST_Hookswitch;
      task.next_ms = curtime + T_HOOK_Hookswitch;
      break;

    case HOST_Hookswitch:
      set_hook(task.active_index, true); // End Hookswitch
      task.state = CLEANUP;
      task.next_ms = curtime + T_STABILIZE;
      break;

    case CLEANUP:
      line_ctrl_mux_select(0); // Release Line Control
      task.state = IDLE;
      break;
  }
}

void check_buttons() {
  if (task.state != IDLE) return;

  digitalWrite(transfer_shiftld_pin, LOW);
  delayMicroseconds(5);
  digitalWrite(transfer_shiftld_pin, HIGH);
  
  digitalWrite(transfer_shiftinh_pin, LOW);
  for (int i = 0; i < NUM_TRANSFER_BTNS; i++) {
    bool pressed = !digitalRead(transfer_shiftout_pin);
    if (pressed) {
      task.active_index = i; // Save which phone triggered this
      task.state = LOCAL_PICKUP;
      break; 
    }
    digitalWrite(transfer_shiftclk_pin, HIGH);
    delayMicroseconds(5);
    digitalWrite(transfer_shiftclk_pin, LOW);
  }
  digitalWrite(transfer_shiftinh_pin, HIGH);
}

void setup() {
  for (auto p : line_ctrls) pinMode(p, OUTPUT);
  for (auto p : offhook_ctrls) {
    pinMode(p, OUTPUT);
    digitalWrite(p, HIGH); // On-hook by default
  }
  
  pinMode(transfer_shiftout_pin, INPUT);
  pinMode(transfer_shiftld_pin, OUTPUT);
  pinMode(transfer_shiftclk_pin, OUTPUT);
  pinMode(transfer_shiftinh_pin, OUTPUT);
  
  digitalWrite(transfer_shiftinh_pin, HIGH);
  digitalWrite(transfer_shiftld_pin, HIGH);
}

void loop() {
  curtime = millis();
  check_buttons();
  run_sequence();
}

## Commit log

2026-02-06 picked new MCU and updated some part numbers
2026-02-06 add external power circuitry for mcu
2026-02-07 drew schematic of naive wiretap circuit
2026-02-10 add footprints and part numbers for power caps
2026-02-10 add more supporting external circuitry for the MCU
2026-02-10 add external flash chip
2026-02-10 updated annotation on wiretap board
2026-02-13 added relays and wiretap circuits to schematic
2026-02-13 fixed minor mistake on relay sch
2026-02-24 added multiplexer and updated relay notation
2026-02-26 added adc sheet
2026-02-26 remove MCU and add symbols for stm32 nucleo morpho connectors
2026-02-26 update the symbols for the nucleo pins
2026-02-26 make nucleo pins a shared symbol with units
2026-02-26 updated multiplexer with busses, added ADCs, fixed relay sch
2026-03-03 working on duplicating adc and control circuits between phone jacks
2026-03-03 finished jack hierachial labels. started putting them on the main sch
    (pts
    (xy 45.72 86.36) (xy 59.69 86.36)
    )
    (stroke (width 0) (type default))
    (uuid "8ace12cb-ee30-47b7-8bb3-4f75477c25bd")
    )
2026-03-03 add new gnd pins to nucleo symbol
2026-03-05 add footprint for stm32
2026-03-05 wired data lines on sch
2026-03-09 assigned footprints, added components to pcb
2026-03-11 clean up & organize schematic
2026-03-11 begin organizing the pcb components for layout
2026-03-12 commenced placement on pcb
2026-03-18 add SPDT relay footprint and update symbol for it
2026-03-18 fix nucleo footprint and update pin numbers
2026-03-24 remove old power sheet
2026-03-24 add part numbers for remaining important parts
2026-03-24 initial column wiring
2026-03-24 start adding shift registers for signalling
2026-03-24 more shift register work
2026-03-24 mostly finished wiring one column
2026-03-25 shift register page assembled for 16 phones
2026-03-25 forgot to connect SR to nucleo
2026-03-25 organize jacks in the pcb layout
2026-03-25 try organizing supporting components for first and second input jacks
2026-03-26 initial module structure, for tiling later
2026-03-26 module modularized
2026-03-26 added solderjumpers for the control relays
2026-03-26 quickly try laying out pcb with plugins
2026-03-27 copy pasted traces
2026-03-27 holy crap trace routing speedrun
2026-03-27 route EVERYTHING except power planes (ive lost track of how many hours ive been here)
2026-03-27 redid wiring in order to make power planes doable
2026-03-27 add nice silkscreen
2026-03-27 SPLIT THE BOARD IN HALF
2026-03-27 run track and via cleanup
2026-03-27 shrink edge cuts a little bit
2026-04-02 add stm32 platformio code
2026-04-02 update gitignore
2026-04-02 fix pin typo with nucleo symbol
2026-04-02 start adding code for handling transfer call buttons/shift registers
2026-04-07 more preliminary work on shift register support
2026-04-07 add untested implementation of shift register reading
2026-04-07 start implementing SPI code for the ADCs
2026-04-10 update to kicad 10 & fix nucleo symbol to use background color
2026-04-10 more SPI work for the ADCs
2026-04-10 wrapping up for the night on ADC stuff
2026-04-10 basic ADC polling code
2026-04-10 fix incorrect indexing for sample buffer
2026-04-10 call number when transfer button pressed and serially print adc samples
2026-04-10 add dedicated serial data transfer function
2026-04-14 start working on pi serial connection code
2026-04-14 update gitignore and project files
2026-04-23 Various debugging while getting ADCs to work. ADCs now output plain text
2026-04-24 fixed the shift register control logic. The registers are now read properly
2026-04-24 fix return statement instead of continue in process_dialing
2026-04-24 changed line control mux to reflect actual implementation, and did initial implementation of modified dial system.
2026-04-25 implemented call transferring, appears to work but needs to be proven.
2026-04-25 updated phone numbers
2026-04-25 start adding code refactor for telethon
2026-04-25 refactor part 1.1
2026-04-25 Hacked together call transfer to baird and jk audio. can't do further because we can't hang up a phone intentionally without hanging up all.
2026-04-25 brah
2026-04-25 modified file structure
2026-04-25 use old transfer button logic
2026-04-28 Got call transferring working
2026-04-28 reduced timings for faster transfer.
